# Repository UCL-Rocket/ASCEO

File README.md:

# ASCEO
Aerial Spinning Camera Experiment for Observation ("formerly Project Philo") - a camera payload that provides stable video footage from within a rocket.

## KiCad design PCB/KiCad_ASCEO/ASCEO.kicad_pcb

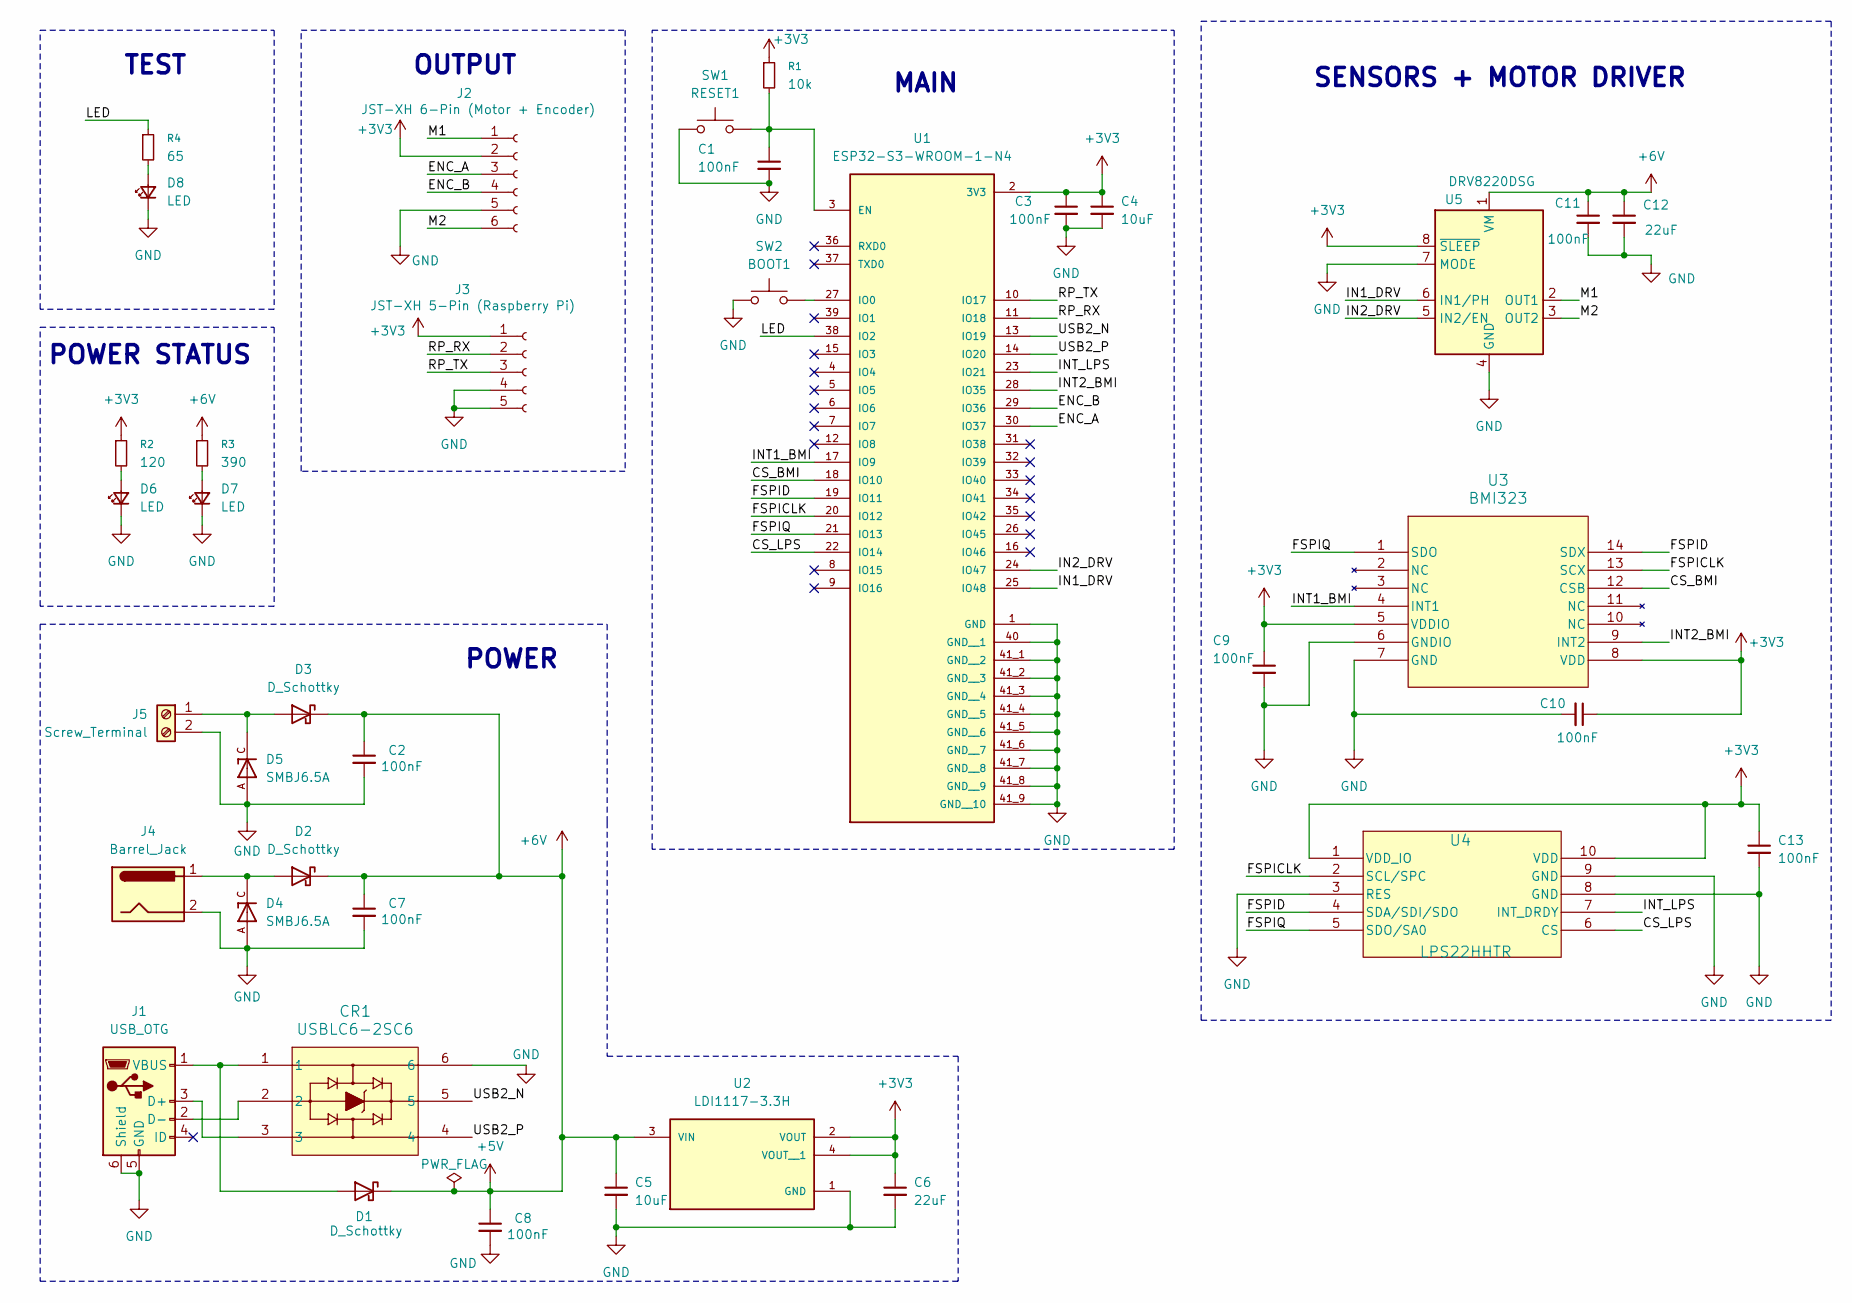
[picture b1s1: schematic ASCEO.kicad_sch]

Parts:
C1, C2, C3, C7, C8, C9, C10, C11, C13: 100nF; C_0603_1608Metric_Pad1.08x0.95mm_HandSolder
C4, C5: 10uF; C_0805_2012Metric_Pad1.18x1.45mm_HandSolder
C6, C12: 22uF; CP_Radial_D12.5mm_P5.00mm
CR1: USBLC6-2SC6; SOT23-6L_STM
D1, D2, D3: D_Schottky; D_SMA_Handsoldering
D4, D5: SMBJ6.5A; DIOM4336X265N; PARTREV F2102
D6, D7, D8: LED; LED_0805_2012Metric_Pad1.15x1.40mm_HandSolder
J1: USB_OTG; CON00317_5_MOL
J2: JST-XH 6-Pin (Motor + Encoder); JST_XH_B6B-XH-A_1x06_P2.50mm_Vertical
J3: JST-XH 5-Pin (Raspberry Pi); JST_XH_B5B-XH-A_1x05_P2.50mm_Vertical
J4: Barrel_Jack; SAMESKY_PJ-073
J5: Screw_Terminal; CUI_TB002-500-02BE
R1: 10k; R_0805_2012Metric_Pad1.20x1.40mm_HandSolder
R2: 120; R_0603_1608Metric_Pad0.98x0.95mm_HandSolder
R3: 390; R_0603_1608Metric_Pad0.98x0.95mm_HandSolder
R4: 65; R_0603_1608Metric_Pad0.98x0.95mm_HandSolder
SW1: RESET1; SW_SWT0210-045026GSA_REVA
SW2: BOOT1; SW_SWT0210-045026GSA_REVA
U1: ESP32-S3-WROOM-1-N4; ESP32-S3-WROOM-1; PARTREV v1.0
U2: LDI1117-3.3H; SOT-223; PARTREV N/A
U3: BMI323; BMI323_BOS
U4: LPS22HHTR; HLGA-10L_2X2X0P73_STM
U5: DRV8220DSG; WSON8_DSG_TEX

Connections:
+3V3: C3.1, C4.1, C6.1, C9.1, C10.1, C13.1, J2.2, J3.1, R1.1, R2.1, U1.2 (3V3), U2.2 (VOUT), U2.4 (VOUT__1), U3.5 (VDDIO), U3.8 (VDD), U4.1 (VDD_IO), U4.10 (VDD), U5.8 (~SLEEP)
+5V: C2.1, C5.1, C7.1, C8.1, C11.1, C12.1, D1.1 (K), D2.1 (K), D3.1 (K), R3.1, U2.3 (VIN), U5.1 (VM)
/CS_BMI: U1.18 (IO10), U3.12 (CSB)
/CS_LPS: U1.22 (IO14), U4.6 (CS)
/ENC_A: J2.3, U1.30 (IO37)
/ENC_B: J2.4, U1.29 (IO36)
/FSPICLK: U1.20 (IO12), U3.13 (SCX), U4.2 (SCL/SPC)
/FSPID: U1.19 (IO11), U3.14 (SDX), U4.4 (SDA/SDI/SDO)
/FSPIQ: U1.21 (IO13), U3.1 (SDO), U4.5 (SDO/SA0)
/IN1_DRV: U1.25 (IO48), U5.6 (IN1/PH)
/IN2_DRV: U1.24 (IO47), U5.5 (IN2/EN)
/INT1_BMI: U1.17 (IO9), U3.4 (INT1)
/INT2_BMI: U1.28 (IO35), U3.9 (INT2)
/INT_LPS: U1.23 (IO21), U4.7 (INT_DRDY)
/LED: R4.1, U1.38 (IO2)
/M1: J2.1, U5.2 (OUT1)
/M2: J2.6, U5.3 (OUT2)
/RP_RX: J3.2, U1.11 (IO18)
/RP_TX: J3.3, U1.10 (IO17)
/USB2_N: CR1.5, U1.13 (IO19)
/USB2_P: CR1.4, U1.14 (IO20)
GND: C1.2, C2.2, C3.2, C4.2, C5.2, C6.2, C7.2, C8.2, C9.2, C10.2, C11.2, C12.2, C13.2, CR1.6, D4.A, D5.A, D6.1 (K), D7.1 (K), D8.1 (K), J1.5 (GND), J1.6 (Shield), J2.5, J3.4, J3.5, J4.2, J5.2, SW1.1, SW2.1, U1.1 (GND), U1.40 (GND__1), U1.41_1 (GND__2), U1.41_2 (GND__3), U1.41_3 (GND__4), U1.41_4 (GND__5), U1.41_5 (GND__6), U1.41_6 (GND__7), U1.41_7 (GND__8), U1.41_8 (GND__9), U1.41_9 (GND__10), U2.1 (GND), U3.6 (GNDIO), U3.7 (GND), U4.3 (RES), U4.8 (GND), U4.9 (GND), U5.4 (GND), U5.7 (MODE), U5.9 (GND); also elsewhere on the board
unnamed: CR1.1, D1.2 (A), J1.1 (VBUS)
unnamed: D2.2 (A), D4.C, J4.1
unnamed: D3.2 (A), D5.C, J5.1
unnamed: D6.2 (A), R2.2
unnamed: D7.2 (A), R3.2
unnamed: D8.2 (A), R4.2
unnamed: CR1.3, J1.3 (D+)
unnamed: CR1.2, J1.2 (D-)
unnamed 30: C1.1, R1.2, SW1.2, U1.3 (EN); also elsewhere on the board
unnamed 31: SW2.2, U1.27 (IO0); also elsewhere on the board

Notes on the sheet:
POWER STATUS
POWER
OUTPUT
MAIN
TEST
SENSORS + MOTOR DRIVER

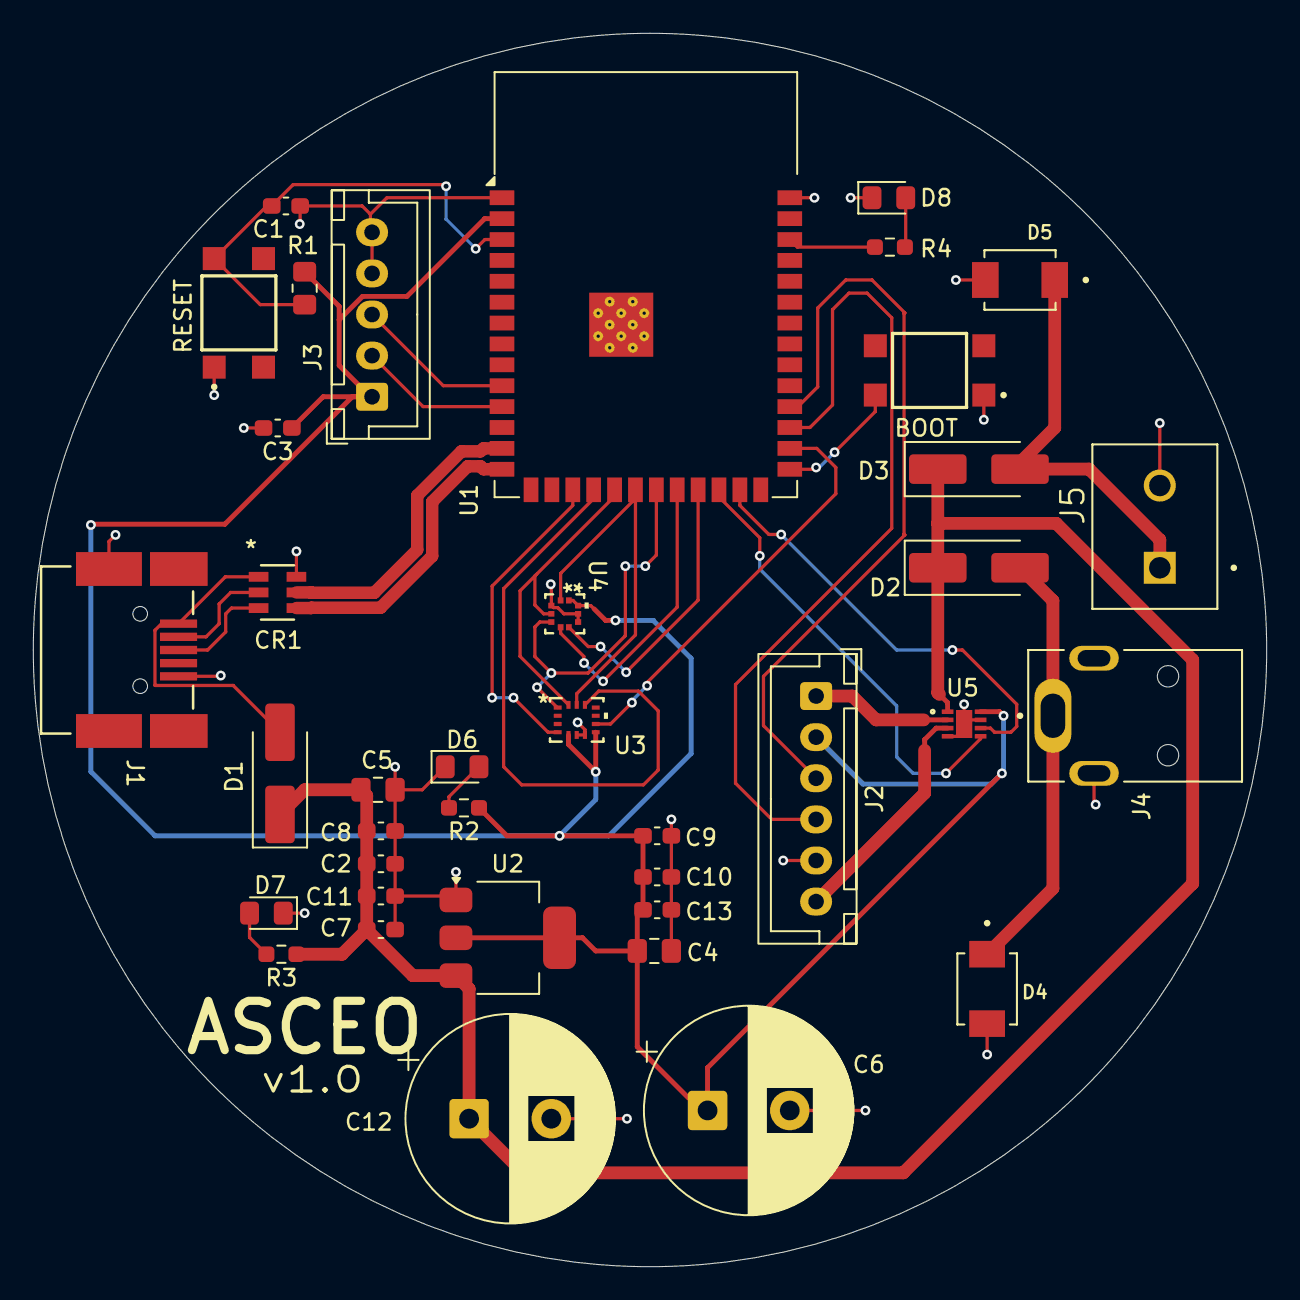
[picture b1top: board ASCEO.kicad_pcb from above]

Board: 2 copper layers, 75.0 x 75.0 mm, 38 parts (0 on the bottom side), 32 nets.

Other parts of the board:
BOOT: BOOT1; SW_SWT0210-045026GSA_REVA
RESET: RESET1; SW_SWT0210-045026GSA_REVA

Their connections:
GND: BOOT.1, RESET.1; also elsewhere on the board
unnamed 30: RESET.2; also elsewhere on the board
unnamed 31: BOOT.2; also elsewhere on the board

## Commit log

2026-01-22 Initial Setup
2026-01-29 Component Additions
2026-01-29 Update 290126 1
2026-01-30 300126 Rev1
2026-01-31 First Draft Schematic
2026-02-01 Footprint Refresh
2026-02-01 First PCB!
2026-02-02 Gerber and Drilling Files
2026-02-03 Initial Arduino Software Testing
2026-02-07 Arduino Testing
